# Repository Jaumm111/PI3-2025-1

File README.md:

# Sistema de classificação de maçãs. Projeto Integrador 3 - Engenharia Eletrônica
Alunos:   
  * Kenner Marqueti Couto  
  * Brian Lesllie Silva Azevedo
  * João Victor Maciel da Veiga

## Cronograma

|Etapa 1|24/04||Etapa 2|15/05||Etapa 3|22/06||Etapa 4|24/07|
|---|---|---|---|---|---|---|---|---|---|---|
|S1|G1||S2|G2||S3|G3||S4|G4|
| Definição geral do funcionamento | Introdução do projeto || Capturar imagens no esp | Código relativo ao funcionamento da camera || Testes de acionamentos | Documentação dos testes de acionamento || Validar treinamento do processamento de imagem (finalizar treinamento do modelo) | Documentar o treinamento |
| Esboço inicial da parte mecânica | Justificativa/motivação || Verificar funcionamento inicial da parte eletrônicamecânica | Justificativa da escolha de base de dados || Iniciar treinamento do processamento de imagem e obtenção de resultados preliminares | Resultados iniciais do treinamento do modelo de aprendizagem || Ajustes finais para sincronização do sistema || Documentar resultados da separação das frutas e assertividade | Documentar estrutura eletromecânica realizada |
| Levantamento e listagem do hardware | Pesquisa do estado da arte (revisão de literatura e outras referências) || Análise e justificativa do processamento (rede neural ou imagem) | Sincronizar atuadores || | || Separar as frutas corretamente ||
| Diagrama de blocos |Listagem dos componentes || Selecionar processamento ou modelo de aprendizagem | Estrutura fisica da seletora || | || | |
||Esboço inicial da parte mecânica|| Seleção de base de dados | | || | || | |
||Levantamento e listagem do hardware || | || | || | |
||Diagrama de blocos com explicação || | || | || | |

## Introdução

Este projeto propõe o desenvolvimento de um robô seletor de maçãs, utilizando-se de um sistema embarcado composto por microcontrolador, câmera, atuadores, e sistemas acessórios (iluminação, alimentação, sensores). Através de processamento de imagens, o robô classifica e seleciona maçãs de diferentes tipos com base em suas características visuais. O objetivo deste projeto é oferecer a pequenos negócios uma alternativa de baixo custo aos equipamentos industriais com finalidade semelhante, tornando a tecnologia mais acessível a negócios de pequeno porte.

## Justificativa

Com a crescente utilização de ferramentas de visão computacional na indústria e comércio, nota-se o uso destes na seleção de mercadorias. Observando a forma com que a seleção de frutas é feita em indústria, constata-se o uso de sistemas complexos e caros.

Enquanto um produto de alto custo possa oferecer velocidade, robustez e precisão importantes para indústrias de larga escala, uma versão mais barata do sistema abre margem para aplicação por empresas menores, incluindo agricultura familiar, e com outras finalidades.

Com isso em mente a equipe visa o desenvolvimento de um sistema de seleção de frutas com visão computacional de hardware mais simples e barato, expandindo a possibilidades de uso para pequenos agricultores, supermercados, e outros empreendimentos de menor porte.

## Estado da arte

Antes do inicio de grandes projetos, é habitual realizar-se uma pesquisa sobre o estado da arte, levantando artigos acadêmicos, patentes e produtos relevantes ao objeto de projeto. Realizou-se então essa busca para sistemas de seleção de maçãs e outras frutas, com enfoque nos métodos utilizados para a classificação.

Constatou-se durante esta pesquisa que a vanguarda da tecnologia usa para além de imagens RGB capturadas por sensores CCD convencionais no espectro de luz visível, imagens de amplo espectro, análise espectroscópica, raio-x e mapeamento tridimensional. Sendo por exemplo a análise de infravermelho utilizada para detecção de infestações de insetos no interior da fruta e a região do infravermelho próximo utilizada para determinação da quantidade de açúcar presente no interior da fruta. [^1] [^2] [^3]

Entretanto estes tipos de análise dependem de componentes muito mais caros que o planejado para uso no projeto, o que inviabilizaria tanto o desenvolvimento devido aos custos quanto a comercialização do produto ao público alvo. Portanto a pesquisa passou a ter como enfoque publicações que utilizassem apenas análise de espectro visível. Estas análises costumam avaliar diferentes métodos computacionais para a classificação.

Os métodos observados podem ser classificados em 3 categorias: métodos clássicos, métodos de aprendizado de máquina não neurais, e métodos de aprendizado de máquina com redes neurais computacionais. Métodos clássicos de visão computacional como OTSU thresholding, Local Binary Patterns (LBP), e técnicas de manipulação de espaço de cor são utilizadas de forma complementar às técnicas de aprendizado de máquina ou em aplicações mais específicas, como por exemplo extração de texturas da casca das frutas. Alguns dos métodos de aprendizado de máquina recorrentes são: Support Vector Machines, Fuzzy Inference System, K-Nearest Neighbors, e Redes Neurais Convolucionais.[^3][^4][^5]

Destaca-se que a bibliografia consultada abrange diferentes sitemas de classificação, desde sistemas que passam a fruta por uma câmara de ambiente controlado e sensores diversos, até sistemas que avaliam a fruta ainda antes da colheita. Portanto é necessária uma profunda análise dos desempenhos e requisitos de cada algoritmo e dos requisitos específicos do projeto antes da escolha do método de classificação, visto que o custo computacional e o trabalho de desenvolvimento ou treinamento, assim como tamanho necessário da base de dados e sensibilidade a variações de ambiente ou amostras ruins na base de treinamento varia drásticamente.

## Princípio de funcionamento

O robô será composto por uma esteira inclinada, um sistema embarcado para aquisição de dados, processamento e acionamentos, além de portinholas controladas. Ao passar pelo sistema, a maçã é classificada de acordo com seu tipo, e a portinhola do recipiente para este respectivo tipo é acionada. Ao fim da esteira há uma abertura para onde irão objetos que não foram classificados em uma das categorias predefinidas.

## Componentes
Para o circuito foram levantados os seguintes componentes:
|Módulo|Quantidade|
|---|---|
|ESP32S3|1|
|Módulo de Câmera OV2640 ou OV5640|1|
|Motor de Passo|3|
|Motor DC|2|
|Esteira|1|
|IR Module(HW-201)|3|

Os motores de passo serão utilizados no acionamento das portas de seleção das frutas, já os motores DC farão a movimentação da esteira. A câmera vai capturar a imagem da fruta e o ESP32S3 fará o processamento da imagem e mandará o sinal de controle para os motores que acionarão as portas seletoras.

## Diagrama de Blocos

Como ideia inicial de projeto a esteira estará em funcionamento continuo e a fruta sempre vai sair alguma identificação seja correto ou não

## Links úteis

[USO DE VISÃO COMPUTACIONAL PARA RECONHECIMENTO DE IMAGENS DE FRUTAS EM IMAGENS RGB](https://repositorio.ufc.br/bitstream/riufc/64490/1/2022_tcc_jkopereira.pdf)

[Classificação de variedades de uma fruta: aplicação computacional em maçãs](https://sbic.org.br/wp-content/uploads/2023/10/pdf/CBIC_2023_paper009.pdf)

[Classificação e reconhecimento de frutos por processamento digital de imagem para previsão da produção](https://www.google.com/url?sa=t&source=web&rct=j&opi=89978449&url=https://ubibliorum.ubi.pt/bitstream/10400.6/7849/1/5700_11911.pdf&ved=2ahUKEwjA2_Tzh-CMAxUHF1kFHUCUKW4QFnoECBYQAQ&usg=AOvVaw3SoWpXwsvYiiUwejJIGhTX)

# Segunda Etapa

## Escolha do Processamento

Comparando-se os fatores requisitos de hardware, tempo de desenvolvimento, treinamento necessário, optou-se por utilizar o método de aprendizado de máquina de rede neural convolucional(CNN) para a classificação das imagens, pois para análise de imagens dentre os três métodos principais são Arvore aleatória de decisão ( Random Forest) , Máquina de Vetores de Suporte(SVM) e rede neural convolucional(CNN) os outros dois métodos precisam de parâmetros mais determinados para encontrar padrões enquanto CNN consegue achar os padrões mais facilmente poupando tempo para o treinamento e criação do algoritmo.

### Escolha do modelo

O modelo You Only look Once(YOLO) versão YOLOv5n (nano) foi escolhida por ser uma das mais leves e otimizadas em termos de desempenho e precisão. Essas versões do YOLOv5 são adequadas para rodar em dispositivos com recursos limitados, como o ESP32, sem comprometer a qualidade da classificação. Ao avaliar alternativas, consideramos dois outros modelos populares: o MobileNet SSD e o Tiny YOLOv4. O MobileNet SSD é um modelo também otimizado para dispositivos embarcados, com uma versão quantizada que é bem leve e rápida. No entanto, ele tende a ser menos preciso do que o YOLOv5, especialmente quando se trata de detectar múltiplos objetos em imagens complexas. O Tiny YOLOv4, por outro lado, é uma versão mais compacta do YOLOv4, mas não é tão otimizada quanto o YOLOv5n, além de ser mais difícil de adaptar ao ESP32 devido ao seu tamanho maior e à necessidade de mais otimizações.

### Escolha da Base de dados

Para o treinamento do modelo é necessária uma base de dados, que foi definido como a base disponível nesse  [link](https://www.kaggle.com/datasets/chrisfilo/fruit-recognition?select=Apple) essa base de dados já oferece uma coleção de imagens rotuladas que cobrem diversas variações de maçãs, o que é crucial para a tarefa de classificação de tipos de maçãs. A diversidade das imagens e a rotulagem correta de diferentes tipos de maçãs permitem que o modelo aprenda a identificar características específicas de cada variedade.

## Captura de Imagem
### Ferramentas Utilizadas

| Componente | Função |
|-----------|--------|
| ESP32-S | Controlador principal, responsável pela comunicação com a câmera|
| Câmera OV2640 | Sensor de imagem |
| Driver CH340 / Cabo USB-A para micro USB-B | Interface de programação e depuração serial entre o computador e o ESP32 |
| VSCode + Extensão ESP-IDF | Ambiente de desenvolvimento |
| Python + Flask | Servidor local que recebe e salva as imagens enviadas pelo ESP32 |

---

###  Funcionalidades Implementadas

- Inicialização da câmera OV2640
- Configuração dos pinos GPIO para comunicação com a câmera
- Conexão automática à rede Wi-Fi
- Captura de imagem a cada 5 segundos
- Codificação da imagem em formato JPEG
- Envio da imagem via HTTP POST para um servidor local
- Armazenamento da imagem no computador via servidor Python

###  Configuração do Ambiente de Desenvolvimento

### 1. Instalação do ambiente ESP-IDF

- Baixar e instalar o [ESP-IDF](https://docs.espressif.com/projects/esp-idf/en/latest/esp32/get-started/index.html).
- Configurar o ambiente no *VSCode* usando a extensão fornecida pelo fabricante *ESP-IDF*.

### 2. Configuração do projeto

No terminal do VSCode:

idf.py set-target esp32

idf.py menuconfig

Dentro do menuconfig, habilitar:

- *PSRAM*: Component config → ESP32-specific → Support for external, SPI-connected RAM
- *Wi-Fi*: Component config → Wi-Fi
- *Camera Driver*: Component config → Camera driver

Salvar e sair.

---

###  Código do ESP32 

O código realiza as seguintes funções:

1. *Inicializa a câmera*

```
esp_err_t init_camera() {
    esp_err_t err = esp_camera_init(&camera_config);
    if (err != ESP_OK) {
        ESP_LOGE(TAG, "Falha ao inicializar câmera");
        return err;
    }
    return ESP_OK;
}
```

2. *Conecta-se a uma rede Wi-Fi*

```
void wifi_init() {
    ESP_ERROR_CHECK(esp_netif_init());
    ESP_ERROR_CHECK(esp_event_loop_create_default());
    esp_netif_create_default_wifi_sta();

    wifi_init_config_t cfg = WIFI_INIT_CONFIG_DEFAULT();
    ESP_ERROR_CHECK(esp_wifi_init(&cfg));

    esp_event_handler_instance_t instance_any_id;
    esp_event_handler_instance_t instance_got_ip;
    ESP_ERROR_CHECK(esp_event_handler_instance_register(WIFI_EVENT,
                                                        ESP_EVENT_ANY_ID,
                                                        &wifi_event_handler,
                                                        NULL,
                                                        &instance_any_id));
    ESP_ERROR_CHECK(esp_event_handler_instance_register(IP_EVENT,
                                                        IP_EVENT_STA_GOT_IP,
                                                        &wifi_event_handler,
                                                        NULL,
                                                        &instance_got_ip));

    wifi_config_t wifi_config = {
        .sta = {
            .ssid = WIFI_SSID,
            .password = WIFI_PASS,
            .threshold.authmode = WIFI_AUTH_WPA2_PSK,
        },
    };
    ESP_ERROR_CHECK(esp_wifi_set_mode(WIFI_MODE_STA));
    ESP_ERROR_CHECK(esp_wifi_set_config(ESP_IF_WIFI_STA, &wifi_config));
    ESP_ERROR_CHECK(esp_wifi_start());
}
```

3. *Captura uma imagem a cada 5 segundos*

```
        camera_fb_t *fb = esp_camera_fb_get();
        if (!fb) {
            ESP_LOGE(TAG, "Falha ao obter frame da câmera");
            continue;
        }
        ...
        vTaskDelay(pdMS_TO_TICKS(5000));// A cada 5 segundos
```

4. *Envia a imagem via HTTP POST para um servidor local*

```
void send_http_post(uint8_t *image_data, size_t image_len) 
```

### Servidor Python (server.py)

Roda um servidor simples com *Flask* para receber e salvar a imagem.

### Dependências:

pip install flask

###  Passo a Passo para Execução

### 1. Ligar o ESP32-CAM

- Conectar o ESP32-CAM ao computador via cabo USB.
- Selecionar a porta no VSCode.

### 2. Compilar e gravar o firmware

No terminal do VSCode:

idf.py build

idf.py flash

idf.py monitor

### 3. Executar o servidor Python

Em outro terminal:

python server.py

### 4. Verificar a imagem recebida

Após alguns segundos, o ESP32 enviará uma imagem JPEG, que será salva como:

imagem_recebida.jpg

no mesmo diretório onde o script server.py está sendo executado.

## Testes iniciais da parte eletromecânica.

Para o teste da parte eletromecânica, confeccionou-se uma das portas do sistema em MDF. Efetuou-se 4 furos nas laterais, à fim de agirem como eixo pivotante. Mais próximos a limite superior são os furos inicialmente projetados, e os furos inferiores foram realizados para, caso o torque do motor seja insufuciente, reduza-se a alavanca, e portanto, a exigência deste parâmetro. Para fixação do eixo no mdf de forma a evitar a destruição da porta, utilizou-se duas chapas de metal parafusadas de forma a comprimir a peça.

Para os testes do motor de passo *NEMA 17* de código *17HS8401* foi utilizado o ESP32S, um driver *HR4988SQ*, e um driver *DRV8825*, além de fontes de bancada de tensão variável com limitador de corrente ajustável. A atuação com o driver DVR8825 inicialmente funcionou, porém após a troca de um cabo de fonte o driver passou a consumir 150 mA de corrente em seus pinos de controle. Mesmo substituindo por um modelo novo, não obteve-se sucesso em utilizá-lo para o controle. 

Considerando-se em uma aproximação o peso da porta de 200g e o torque do motor de 5,2 Kgf.cm e uma alavanca de 24 cm o motor seria suficiente com pouca margem. Porém esta aproximação considera que o peso estaria todo na ponta da alvanca e não distribuído ao longo de seu comprimento, gerando assim uma margem que prevê o motor como adequado.

Como teste alternativo para a capacidade do motor de suportar o peso alimentou-se o motor diretamente na fonte, limitando sua corrente inicialmente me 400 mA (total para ambas as bobinas) e de forma incremental até 2 A (total para ambas as bobinas). Com valores menores de corrente o motor nao consegue manter a chapa paralela ao chão pivotando em torno do furo mais próximo à extremidade, porém, com 1,8 A o motor se mostrou suficiente.

Relizou-se então testes com o driver *HR4988SQ*, este driver funcionou corretametne, porém apesar de ajustar o trimpot limitador de corrente, este driver não forneceu mais de 400 mA ao motor, o que foi insuficiente para mater o motor travado e perpendicular ao chão. Utilizando, entretanto, o furo mais central, o motor conseguiu mover a porta sem dificuldades. Foram testadas mudanças no microstep na tentativa de angariar mais torque, porém mesmo assim não foi possível utilizar o furo superior.

Testou-se a esteira alimentando-a diretamente com 12V. A esteira funcionou bem sem comentários adicionais.

# Terceira Etapa

## Estrutura física da seletora

Utilizou-se como material uma combinação de MDF, MDP e madeira natural para criar a estrutura composta por:

- 2 portas móveis atuadas por motores de passo e sua estrutura de suporte.
- 1 suporte tipo mesa para fixação da câmera e restante da parte eletrônica.
- 1 cancela para reter o avanço das frutas sub a câmera, possibilitanto girar a fruta.

Todo o material foi doado ou reaproveitado. Encontrou-se inicialmente dificuldades devido à inexperiência com trabalho em madeira, porém significativas evoluções ocorreram. A primeira mesa montada pela equipe, vista na imagem abaixo, ficou bastante torta e pouco estável. Esta mesa foi refeita, com outro material e utilizando-se de outras técnicas de fixação e de design, gerando um resultado muito mais bem acabado e estável.

A nova mesa pode ser vista na imagem abaixo, além de uma estrutura mais reforçada, o método de fixação deixou de ser pregos e passou a ser parafusos transpassados e porcas.

Foram também feitas as portas que serão responsáveis por impedir que as maçãs caiam nos compartimentos errados. Essas portas podem ser vistas na imagem abaixo.

## Treinamento e implementação de modelo

### Treinamento inicial

Utilizando-se do google colab treinou-se um modelo YOLOv 5S com a base de dados selecionada na etapa 2, em testes utilizando imagens de alta resolução e sem pré-processamento algum o modelo apresentou uma alta taxa de falsos positivos, o modelo não foi testado com muitas imagens ou com pré-processamento. O modelo levou 11 ms para classificar uma imagem de alta resolução em um computador desktop.

Um breve snippet do trinamento pode ser visto abaixo

```

```

### Implementação

Por não apresentar resultados satisfatórios este modelo não foi implementado no ESP, optando-se por implementar um modelo pré treinado para verificar a viabiliade do ESP escolhido para a classificação.

Implementou-se então um modelo pré treinado que classifica parafusos em 3 categorias: pequeno, grande e preto. O modelo foi pré treinado com 300 epochs, sendo apenas um modelo exemplo, ele foi capaz de distinguir parafusos de outros objetos, e apresentou performance satisfatória para os testes iniciais em classificar por tamanho. O modelo pré treinado levou 1,4 segundos para classificar uma imagem, indicando que ou otimizações serão necessárias, ou será necessário o uso de hardware mais potente para o produto final.

Uma breve demonstração pode ser vista abaixo.

## Teste dos acionamentos

Testou-se individualmente os acionamentos nas portas e na cancela e peorcebeu-se que não é necessário que as portas fiquem paralelas ao chão, e que ao tentar fazê-lo, o motor de passo não tem força suficiente e a porta acaba caindo, possíveis soluções são alívio de peso da porta e a substituição do motor por um mais forte. Entretanto o motor consegue manter a porta aberta o suficiente para permitir a passagem de uma fruta, e portanto o desenvolvimento pod seguir sem grandes alterações.

A esteira foi acionada com sucesso utilizando-se do esp, e de 2 transistores, 1 2N7000 atuando como driver e um IRF540N. O esquematico do circuito pode ser visto abaixo, bem como seu funcionamento.

A cancela também foi acionada sem problemas.

## Sinconização dos atuadores
Para os testes iniciais de sinconização programou-se uma rotina temporizada da seguinte forma: abre-se cancela e porta e aciona-se a esteira -> fecha-se a cancela -> fecha-se a porta e para-se a esteira. Este funcionamento pode ser visto no GIF abaixo.

# Quarta etapa

## Confecção da PCB

Para a integração entre o processamento e acionamentos foi elaborada uma PCB, com o papel de conectar o ESP aos drivers e demais componentes, e de fornecer as devidas interfaces de conexão bem como alimentação para os componentes.

O layout inicial da PCB pode ser visto abaixo.

A PCB completa pode ser vista na imagem abaixo.

## Treinamento do Modelo

Para o treinamento adequado do modelo utilizou-se [deste](https://www.kaggle.com/datasets/chrisfilo/fruit-recognition/data) do banco de imagens e da plataforma [Roboflow](https://app.roboflow.com/), esta plataforma permite a criação de um projeto, upload da base de dados, e oferece ferramentas para gerenciamento do projeto, anotação de imagens e mais. Dentro da plataforma foi criado um projeto, carregado o banco de dados contendo as imagens, separadas as imagens a ser usadas para treinamento, validação e teste, e os membros podem individualmente e independentemente anotar imagens. 

Foram criadas 4 classes para maçãs, sendo elas: nacional (abrangendo gala e fuji), argentina, pink (correspondente ao tipo pink lady) e verde. Até o momento foram classificadas cerca de 1000 imagens sendo que a maioria delas contem mais de uma fruta, forma então classificados aproximadamente mil objetos de cada classe.

O foram feitos mais de 10 treinamentos de modelo, com diferentes parâmetros de resolução e epochs. Os modelos foram treinados no formato YOLO, porém para implementação no microcontrolador se faz necessária sua conversão para TFLite. 

O treinamento dos modelos assim como alguns testes de validação e conversão foram inicialmente feitos neste  [Notebook do Colab](https://colab.research.google.com/drive/1OkuWUN6HiTaSCjiW95Y2XHSDLfaRnJr2?usp=sharing) e posteriormente a conversão foi feita em ambiente local por questões de compatibilidade.

Os treinamentos foram realizados com as imagens em duas resoluções, 96x96 e 640x640. O treinamento com imagens de maior resolução converge muito mais rápido para altas taxas de precisão e recall. Porém o modelo treinado com imagens 96x96 também apresentou boas métricas no fim do treinamento e acabou se desempenhando melhor com imagens do ESP e apresenta menor tempo de treinamento. Precisão mede a taxa de falsos positivos, sendo a taxa de falos positivos = 1 - precisão. E recall mede, dentre todas os elementos relevantes (detecções e classificações que devem ser feitas), quantos realmente foram feitos. Nota-se que ambas estas medidas antingem um platô após um certo número de epochs, com este número dependendo de variáveis de treinamento, sendo este platô próximo de 1. Julgou-se as métricas do modelo treinado com imagens em resolução 640x640 mostrado abaixo como satisfatória, porém diversos treinamentos com outras resoluções e parâmetros foram realizadas e podem ser vistas no [Google Drive](https://drive.google.com/drive/folders/1eUns3YBccAsm3urnZM-7gGBlzAcRlj5u?usp=sharing).

Abaixo está uma imagem com as métricas do modelo treinado com imagens de *640x640*

E abaixo seguem os resultados do modelo trinado com imagens de *96x96*

Os modelos convertidos no ambiente do colab não podiam ser gravados no ESP, sendo necessários ajustes nos parâmetros de treinamento e conversão, a documentação utilizada como base para o projeto e para a conversão se dava em uma toolchain antiga e vários problemas de dependências apareceram ao longo do caminho. Além da instalação manual de pacotes e dependencias em snapshots antigos dos repositórios, foi configurado um ambiente docker para a utilização destes pacotes. Entretanto, posteriormente o problema foi resolvido configurando-se uma toolchain mais antiga em ambiente local em uma das máquinas da equipe.

Além das conversões foi também tentada uma redução em diversos parâmetros de treinamento, porém isso resultou em ua performance muito degradada que não pôde ser utilizada. Abaixo pode-se ver as métricas deste treinamento.

## Testes do modelo

Após o treinamento do modelo, é feita uma validação deste, com imagens do banco de dados separadas especificamente para este propósito. Dentro do dataset base, o modelo treinado apresenta uma taxa de acerto muito próxima de 100%, reconhecendo e classificando corretamente as maçãs. 

Em imagens da internet o desempenho apresenta variações, desempenhando muito bem em imagens com poucas maçãs e fundo uniforme, porém se confundindo um pouco quando há muitas maçãs sobrepostas em imagens de baixa qualidade, maçãs parcialmente maduras às vezes são classificadas como verdes, e há uma certa margem de erro entre maçãs nacionais e a classe pink (variedade Pink Lady).

Abaixo segue a classificação de algumas imagens da internet, mais imagens podem ser encontradas na pasta do [Google Drive](https://drive.google.com/drive/folders/1eUns3YBccAsm3urnZM-7gGBlzAcRlj5u?usp=sharing), as imagens de validação para cada teste se encontram dentro da subpasta runs>detect>nome_do_teste.

## Implementação do modelo no ESP

O modelo convertido foi implementado no ESP, utilizando-se do projeto dos parafusos como base, foi necessária a remoção de uma instrução do modelo para que este pudesse ser gravado no ESP.
Nos testes iniciais o modelo parece sempre ter 50% de certeza que há uma maçã na imagem. Este problema pode ser originário da conversão do modelo ou de algum problema no projeto (inicialização incorreta da câmera por exemplo). Para encontrar a origem do problema foi feito um teste onde o ESP apenas transmite as imagens e roda-se o modelo *já convertido* no computador. Nestes testes averiguou-se que o ultimo modelo treinado e convertido tem uma excelente taxa de reconhecimento de maçãs, porém com uma taxa elevada de falsos positivos. Elevando-se o limiar de certeza para cerca de 95% reduz-se significativamente a taxa de falsos positivos, porém raras vezes outros objetos redondos, como cebolas e laranjas podem ser reconhecidos como maçãs.

Este teste, foi então útil não apenas para constatar que a performance do modelo em TFLite difere da performance do modelo original, como também para aferir que as detecções obtidas no ESP *não* correspondem ao desempenho esperado do modelo, mesmo em sua versão TFLite, os modelos em TFLite devem ser convertidos para um arquivo .cc para a gravação no ESP, sendo esta conversão o provável responsável pelo problema atual.

## Ajustes de sincronização e Eletromecânica.

Um teste final foi feito para garantir que a porta desejada estivesse aberta no momento em que a fruta chega até sua frete, no vídeo abaixo inicialmente a fruta é designada para a primeira porta, em seguida para o fim da esteira (descarte), e por fim para a segunda porta. Um gif do teste pode ser visto abaixo.

O desenvolvimento da parte eletromecânica vem sendo bastante detalhado desde a primeira etapa, sendo assim nesta última etapa bastou confeccionar a PCB detalhada acima e posicioná-la no topo da estrutura conforme visto no GIF acima. Rechonece-se que a estrutura mecânica é o ponto menos desenvolvido do projeto e que caso evolua para um produto deverá ser refeita de forma mais robusta e menos artesanal.

## Propostas de melhoria e soluções

Uma melhoria seria a adição de imagens de outras frutas e de fotos mais diversas ao conjunto de dados de terinamento, isto poderia mitigar a taxa de falsos positivos e melhorar a detecção em imgens com fundos mais diversos.

O processamento de imagem leva cerca de 800 ms para ser executado no ESP, inviabilizando seu uso em uma linha com alto fluxo de frutas, alem disso o modelo deve passar por uma série de conversões e simplificações para rodar adequadamente no esp, o que custa tempo e deteriora sua acertividade. Uma alternativa que soluciona ambos os problemas e torna o sistema mais modular e expansível é a separação da classificação em um outro dispositivo, sendo este um microcontrolador mais potente, um FPGA, ou um SBC como um Raspberry Pi. Desta forma seria possível rodar o modelo completo, que tem acertividade bastante superior, executar a inferência de forma mais rápida, e até mesmo processar múltiplas linhas em um único dispositivo, em uma configuração de múltiplos ESPs para uma unidade de proessamento. 

Além disso um reprojeto mais robusto da parte mecânica seria necessário para viabilidade de produção em escala.

## Referências

[^1]: Borba, K. R., Sapelli, K. S., Spricigo, P. C., & Ferreira, M. D. (2017). Near infrared spectroscopy sugar quantification in intact orange. Citrus Research & Technology, 38(2). https://doi.org/10.4322/crt.ICC118

[^2]: Bahareh Jamshidi, Ability of near-infrared spectroscopy for non-destructive detection of internal insect infestation in fruits: Meta-analysis of spectral ranges and optical measurement modes, Spectrochimica Acta Part A: Molecular and Biomolecular Spectroscopy, Volume 225, 2020, 117479,ISSN 1386-1425, https://doi.org/10.1016/j.saa.2019.117479.

[^3]: Boulley, L et al. 2015. Near-infrared optical spectroscopy of sugar-based mixtures – A snapshot to identify issues of influence. In: Längle, T et al (eds.), OCM 2015 – 2nd International Conference on Optical Characterization of Materials, March 18th – 19th, 2015, Karlsruhe, Germany : Conference Proceedings. Karlsruhe: KIT Scientific Publishing. https://doi.org/10.58895/ksp/1000044906-3 

[^4]: Ji, W.; Wang, J.; Xu, B.; Zhang, T. Apple Grading Based on Multi-Dimensional View Processing and Deep Learning. Foods 2023, 12, 2117. https://doi.org/10.3390/foods12112117

[^5]: Naik, Sapan & Patel, Bankim. (2017). Machine Vision based Fruit Classification and Grading - A Review. International Journal of Computer Applications. 170. 22-34. 10.5120/ijca2017914937.

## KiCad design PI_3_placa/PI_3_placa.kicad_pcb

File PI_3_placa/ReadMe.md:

## Rotear

Abaixo os resultados do roteamento

## Placa

Para confecção da placa foi usado corrosão e transferencia termica no almox, após isso a placa foi furada e soldada

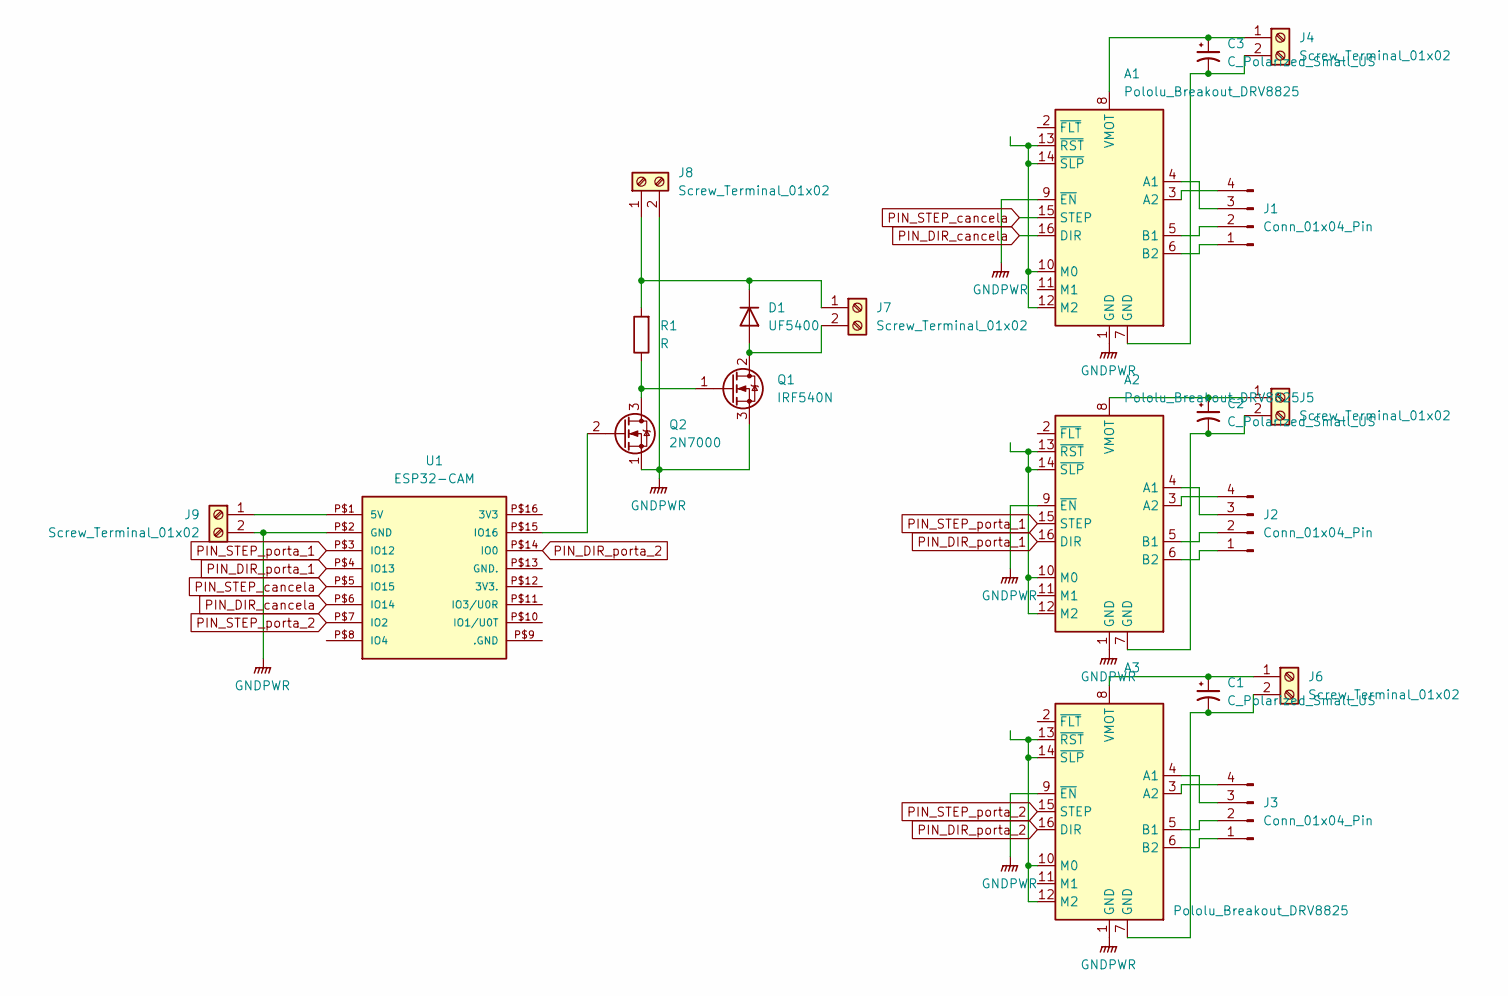
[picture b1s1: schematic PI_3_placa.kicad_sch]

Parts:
A1, A2, A3: Pololu_Breakout_DRV8825; Pololu_Breakout-16_15.2x20.3mm
C1, C2, C3: C_Polarized_Small_US; CP_Radial_D5.0mm_P2.50mm
D1: UF5400; D_DO-201AD_P15.24mm_Horizontal
J1, J2, J3: Conn_01x04_Pin; PinHeader_1x04_P2.54mm_Vertical
J4, J5, J6, J7, J8, J9: Screw_Terminal_01x02; TerminalBlock_Altech_AK300-2_P5.00mm
Q1: IRF540N; TO-220-3_Vertical
Q2: 2N7000; TO-92_Inline
R1: R; R_Axial_DIN0204_L3.6mm_D1.6mm_P7.62mm_Horizontal
U1: ESP32-CAM

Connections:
GNDPWR: A1.1 (GND), A1.9 (~EN), A2.1 (GND), A2.9 (~EN), A3.1 (GND), A3.9 (~EN), J8.2, J9.2, Q1.3 (S), Q2.1 (S), U1.P$2 (GND)
unnamed: A1.4 (A1), J1.3
unnamed: A1.3 (A2), J1.4
unnamed: A1.5 (B1), J1.2
unnamed: A1.6 (B2), J1.1
unnamed: A1.10 (M0), A1.12 (M2), A1.13 (~RST), A1.14 (~SLP)
unnamed: A1.8 (VMOT), C3.1, J4.1
unnamed: A2.4 (A1), J2.3
unnamed: A2.3 (A2), J2.4
unnamed: A2.5 (B1), J2.2
unnamed: A2.6 (B2), J2.1
unnamed: A2.10 (M0), A2.12 (M2), A2.13 (~RST), A2.14 (~SLP)
unnamed: A2.8 (VMOT), C2.1, J5.1
unnamed: A3.4 (A1), J3.3
unnamed: A3.3 (A2), J3.4
unnamed: A3.5 (B1), J3.2
unnamed: A3.6 (B2), J3.1
unnamed: A3.10 (M0), A3.12 (M2), A3.13 (~RST), A3.14 (~SLP)
unnamed: A3.8 (VMOT), C1.1, J6.1
unnamed: D1.2 (A), J7.2, Q1.2 (D)
unnamed: D1.1 (K), J7.1, J8.1, R1.2
unnamed: A1.7 (GND), C3.2, J4.2
unnamed: A2.7 (GND), C2.2, J5.2
unnamed: A3.7 (GND), C1.2, J6.2
unnamed: J9.1, U1.P$1 (5V)
unnamed: Q1.1 (G), Q2.3 (D), R1.1
unnamed: Q2.2 (G), U1.P$15 (IO16)
PIN_DIR_cancela: A1.16 (DIR), U1.P$6 (IO14)
PIN_DIR_porta_1: A2.16 (DIR), U1.P$4 (IO13)
PIN_DIR_porta_2: A3.16 (DIR), U1.P$14 (IO0)
PIN_STEP_cancela: A1.15 (STEP), U1.P$5 (IO15)
PIN_STEP_porta_1: A2.15 (STEP), U1.P$3 (IO12)
PIN_STEP_porta_2: A3.15 (STEP), U1.P$7 (IO2)

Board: 2 copper layers, 20 parts (0 on the bottom side), 33 nets, no tracks yet.

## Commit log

2025-04-08 Update README.md
    Just added Alunos so there is a first commit.
2025-04-08 Update README.md
    Fixed line breaks.
2025-04-24 Adicionada pesquisa do estado da arte e pequenas modificaçoes no README
2025-04-24 added 3d model images
2025-04-24 Adicionadas imagens ao readme
2025-04-24 link Update README.md
2025-05-15 almox fechou
    almox fechando, sry
2025-05-15 upload do codigo ESP32 capturando imagem com a camera
2025-05-15 Update README.md
    decisão de método de processamento
2025-05-15 Update README.md
    captura de imagem
2025-05-15 Update README.md
    captura de imagem 2
2025-06-12 Create uni
2025-06-12 rodando modelo yolov5 no esp32 para detectar parafusos
2025-06-18 Delete
2025-06-26 Rename teste_modelo_treinado_parafusos/application/readme.md to teste_modelo_treinado_parafusos/readme.md
2025-06-26 Update_rotina
2025-07-01 Add_placa
2025-07-03 added sync gif
2025-07-03 adicionados gifs
2025-07-08 adicionada placa para impressao
2025-07-10 added new images for use in readme
2025-07-24 added photos and videos
2025-07-24 added photos
2025-07-24 added code to run model on PC and stream images from ESP
